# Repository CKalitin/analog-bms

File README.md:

# analog-bms
1s2p Li-ion battery module with an analog battery management system (BMS).

### [**Read The Project Blog Post!!**](https://ckalitin.github.io/analogbms/)

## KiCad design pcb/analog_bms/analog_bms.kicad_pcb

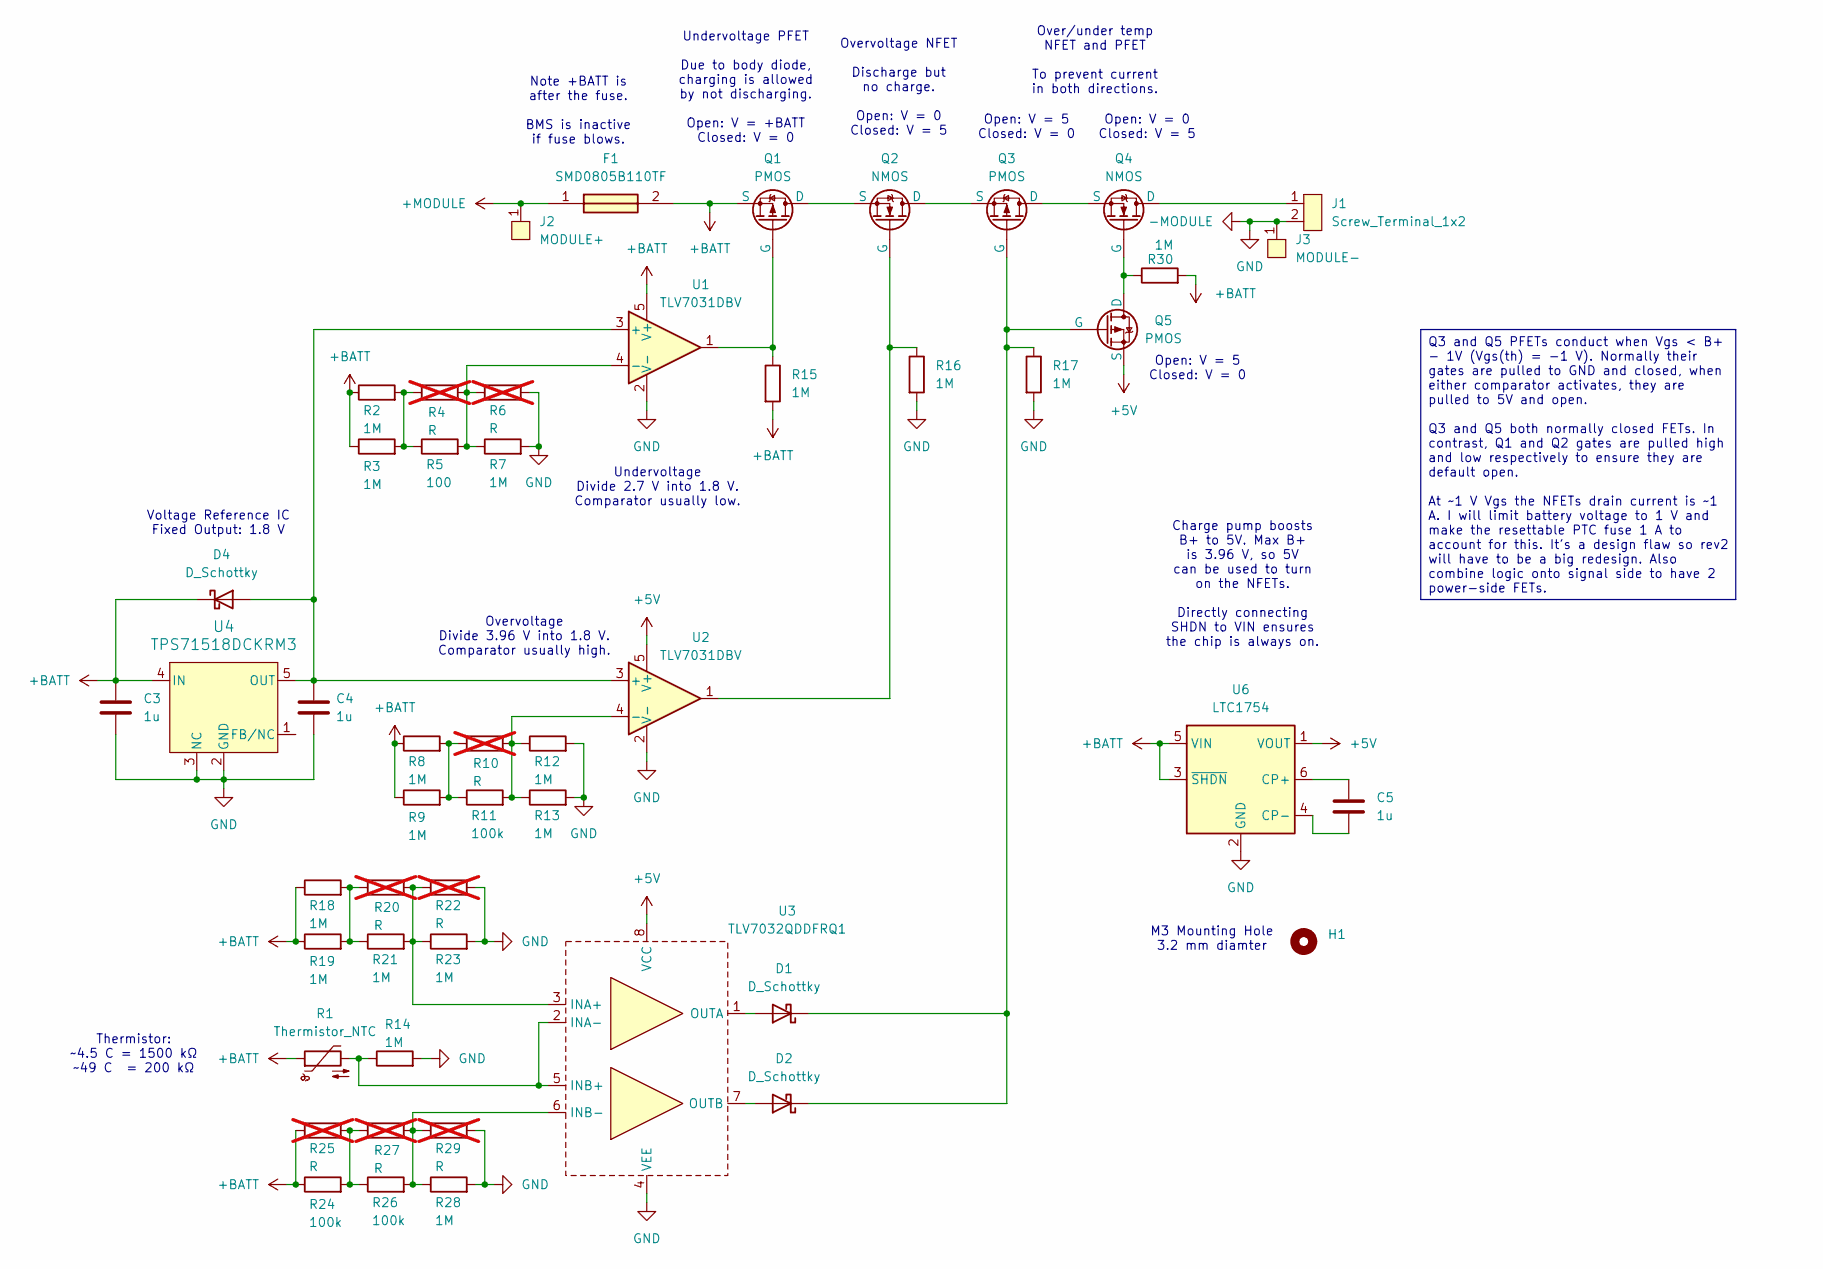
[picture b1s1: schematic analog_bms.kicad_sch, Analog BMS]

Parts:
C3, C4, C5: 1u; C_0805_2012Metric
D1, D2, D4: D_Schottky; D_SOD-323
F1: SMD0805B110TF; R_0805_2012Metric; Mouser Part Number 603-SMD0805B110TF
H1: M3_Mounting_Through_Hole
J1: Screw_Terminal_1x2; 691502710002
J2: MODULE+; 1.5_mm_Through_Hole
J3: MODULE-; 1.5_mm_Through_Hole
Q1, Q3, Q5: PMOS; TSOT_23_No_Arrow
Q2, Q4: NMOS; TSOT_23_No_Arrow
R1: Thermistor_NTC; R_0805_2012Metric
R2, R3, R7, R8, R9, R12, R13, R14, R15, R16, R17, R18, R19, R21, R23, R28, R30: 1M; R_0805_2012Metric
R4, R6, R10, R20, R22, R25, R27, R29: R; R_0805_2012Metric; not fitted
R5: 100; R_0805_2012Metric
R11, R24, R26: 100k; R_0805_2012Metric
U1, U2: TLV7031DBV; SOT-23-5
U3: TLV7032QDDFRQ1
U4: TPS71518DCKRM3
U6: LTC1754; SOT-23-6

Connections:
+5V: Q5.3 (S), U2.5 (V+), U3.8 (VCC), U6.1 (VOUT)
+BATT: C3.1, D4.1 (K), F1.2, Q1.3 (S), R1.1, R2.1, R3.1, R8.1, R9.1, R15.2, R18.1, R19.1, R24.1, R25.1, R30.2, U1.5 (V+), U4.4 (IN), U6.3 (~SHDN), U6.5 (VIN)
+MODULE: F1.1, J2.1
-MODULE: C3.2, C4.2, J1.2, J3.1, R6.2, R7.2, R12.2, R13.2, R14.2, R16.2, R17.2, R22.2, R23.2, R28.2, R29.2, U1.2 (V-), U2.2 (V-), U3.4 (VEE), U4.2 (GND), U4.3 (NC), U6.2 (GND)
unnamed: D1.2 (A), U3.1 (OUTA)
unnamed: D1.1 (K), D2.1 (K), Q3.2 (G), Q5.2 (G), R17.1
unnamed: D2.2 (A), U3.7 (OUTB)
unnamed: C4.1, D4.2 (A), U1.3 (+), U2.3 (+), U4.5 (OUT)
unnamed: Q1.1 (D), Q2.3 (S)
unnamed: Q1.2 (G), R15.1, U1.1
unnamed: Q2.1 (D), Q3.3 (S)
unnamed: Q2.2 (G), R16.1, U2.1
unnamed: Q3.1 (D), Q4.3 (S)
unnamed: J1.1, Q4.1 (D)
unnamed: Q4.2 (G), Q5.1 (D), R30.1
unnamed: R2.2, R3.2, R4.1, R5.1
unnamed: R8.2, R9.2, R10.1, R11.1
unnamed: R18.2, R19.2, R20.1, R21.1
unnamed: R24.2, R25.2, R26.1, R27.1
unnamed: R4.2, R5.2, R6.1, R7.1, U1.4 (-)
unnamed: R10.2, R11.2, R12.1, R13.1, U2.4 (-)
unnamed: R20.2, R21.2, R22.1, R23.1, U3.3 (INA+)
unnamed: R1.2, R14.1, U3.2 (INA-), U3.5 (INB+)
unnamed: R26.2, R27.2, R28.1, R29.1, U3.6 (INB-)
unnamed: C5.1, U6.6 (CP+)
unnamed: C5.2, U6.4 (CP-)

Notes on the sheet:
Voltage Reference IC Fixed Output: 1.8 V
Note +BATT is after the fuse. BMS is inactive if fuse blows.
Open: V = 5 Closed: V = 0
Over/under temp NFET and PFET To prevent current in both directions.
M3 Mounting Hole 3.2 mm diamter
Overvoltage NFET Discharge but no charge. Open: V = 0 Closed: V = 5
Charge pump boosts B+ to 5V. Max B+ is 3.96 V, so 5V can be used to turn on the NFETs. Directly connecting SHDN to VIN ensures the chip is always on.
Undervoltage PFET Due to body diode, charging is allowed by not discharging. Open: V = +BATT Closed: V = 0
Undervoltage Divide 2.7 V into 1.8 V. Comparator usually low.
Overvoltage Divide 3.96 V into 1.8 V. Comparator usually high.
Thermistor: ~4.5 C = 1500 kΩ ~49 C = 200 kΩ
Open: V = 0 Closed: V = 5
Open: V = 5 Closed: V = 0
Q3 and Q5 PFETs conduct when Vgs < B+ - 1V (Vgs(th) = -1 V). Normally their gates are pulled to GND and closed, when either comparator activates, they are pulled to 5V and open. Q3 and Q5 both normally closed FETs. In contrast, Q1 and Q2 gates are pulled high and low respectively to ensure they are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

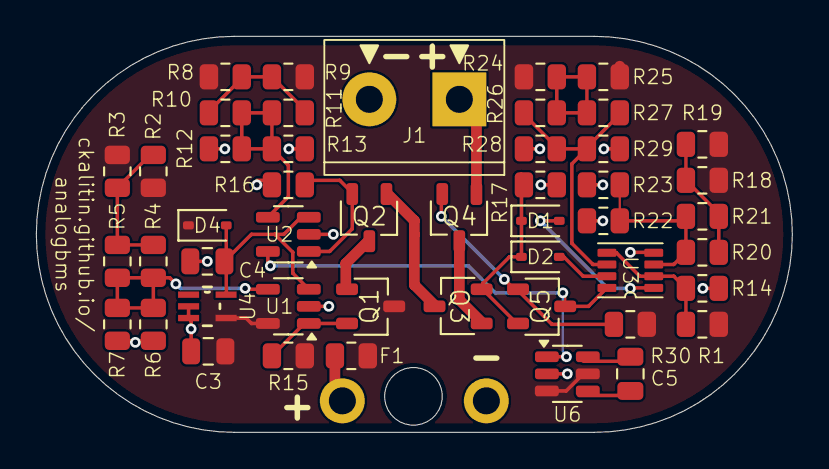
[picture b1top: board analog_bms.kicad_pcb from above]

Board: 2 copper layers, 42.0 x 22.0 mm, 51 parts (0 on the bottom side), 26 nets.

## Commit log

2025-08-19 Schematic rev1
2025-08-19 Printable 18650 + Mounting Hole
2025-08-19 CAD Model
2025-08-20 PCB Design Complete - Pass DRC
    Still skeptical of the DRC. Some very close silk screen elements.
2025-08-20 Black PCB + Renders
2025-08-20 pepes heh
2025-08-20 + & - silkscreen
2025-08-20 Updated rules & solid connection pours
2025-08-24 Fix comparator + pour to track dist
2025-08-24 Digikey, TI, and PCBWay orders!
2025-08-30 Update README with project notes and images
    Added project notes and images to README.
2025-09-21 LTspice sim + attempt at fixing OV UV dividers
2025-09-21 All FET footprints are wrong
2025-09-22 Fixed OV divider & Q3/5 pulldown stronger
2025-09-29 More PCB trace voltage testing
2025-10-05 Update schematic jpg
2025-10-07 README
2025-10-07 nicer order
2025-12-03 Reorganize for rev2
    Man I thought this was gonna be a 3 day speedrun and I'd be done with it
